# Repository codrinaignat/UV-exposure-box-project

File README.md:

# UV-exposure-box-project

Project structure:
- Proteus folder: contains the Proteus simulation of the schematic for the UV exposure box;
- UV_exposure_box_beta and UV_exposure_box folders contain the PCB and schematic of the project in KiCAD; the beta folder is a more recent version of the project;
- uC program folder contains the MPLABX IDE files for the microcontroller, meaning the C code and additional files;
- Necesare.docx is a list of the necessary components in order to build an UV exposure box from scratch. The list is in Romanian;
- UV_exposure_box.pdf is the schematic of the project, in KiCAD.

The project's purpose is to make the PCB creation process easier. The UV exposure is necessary when you want to create a PCB using a photoresist copper board. 
The box has buttons to set the exposure time, to start and stop the exposure.

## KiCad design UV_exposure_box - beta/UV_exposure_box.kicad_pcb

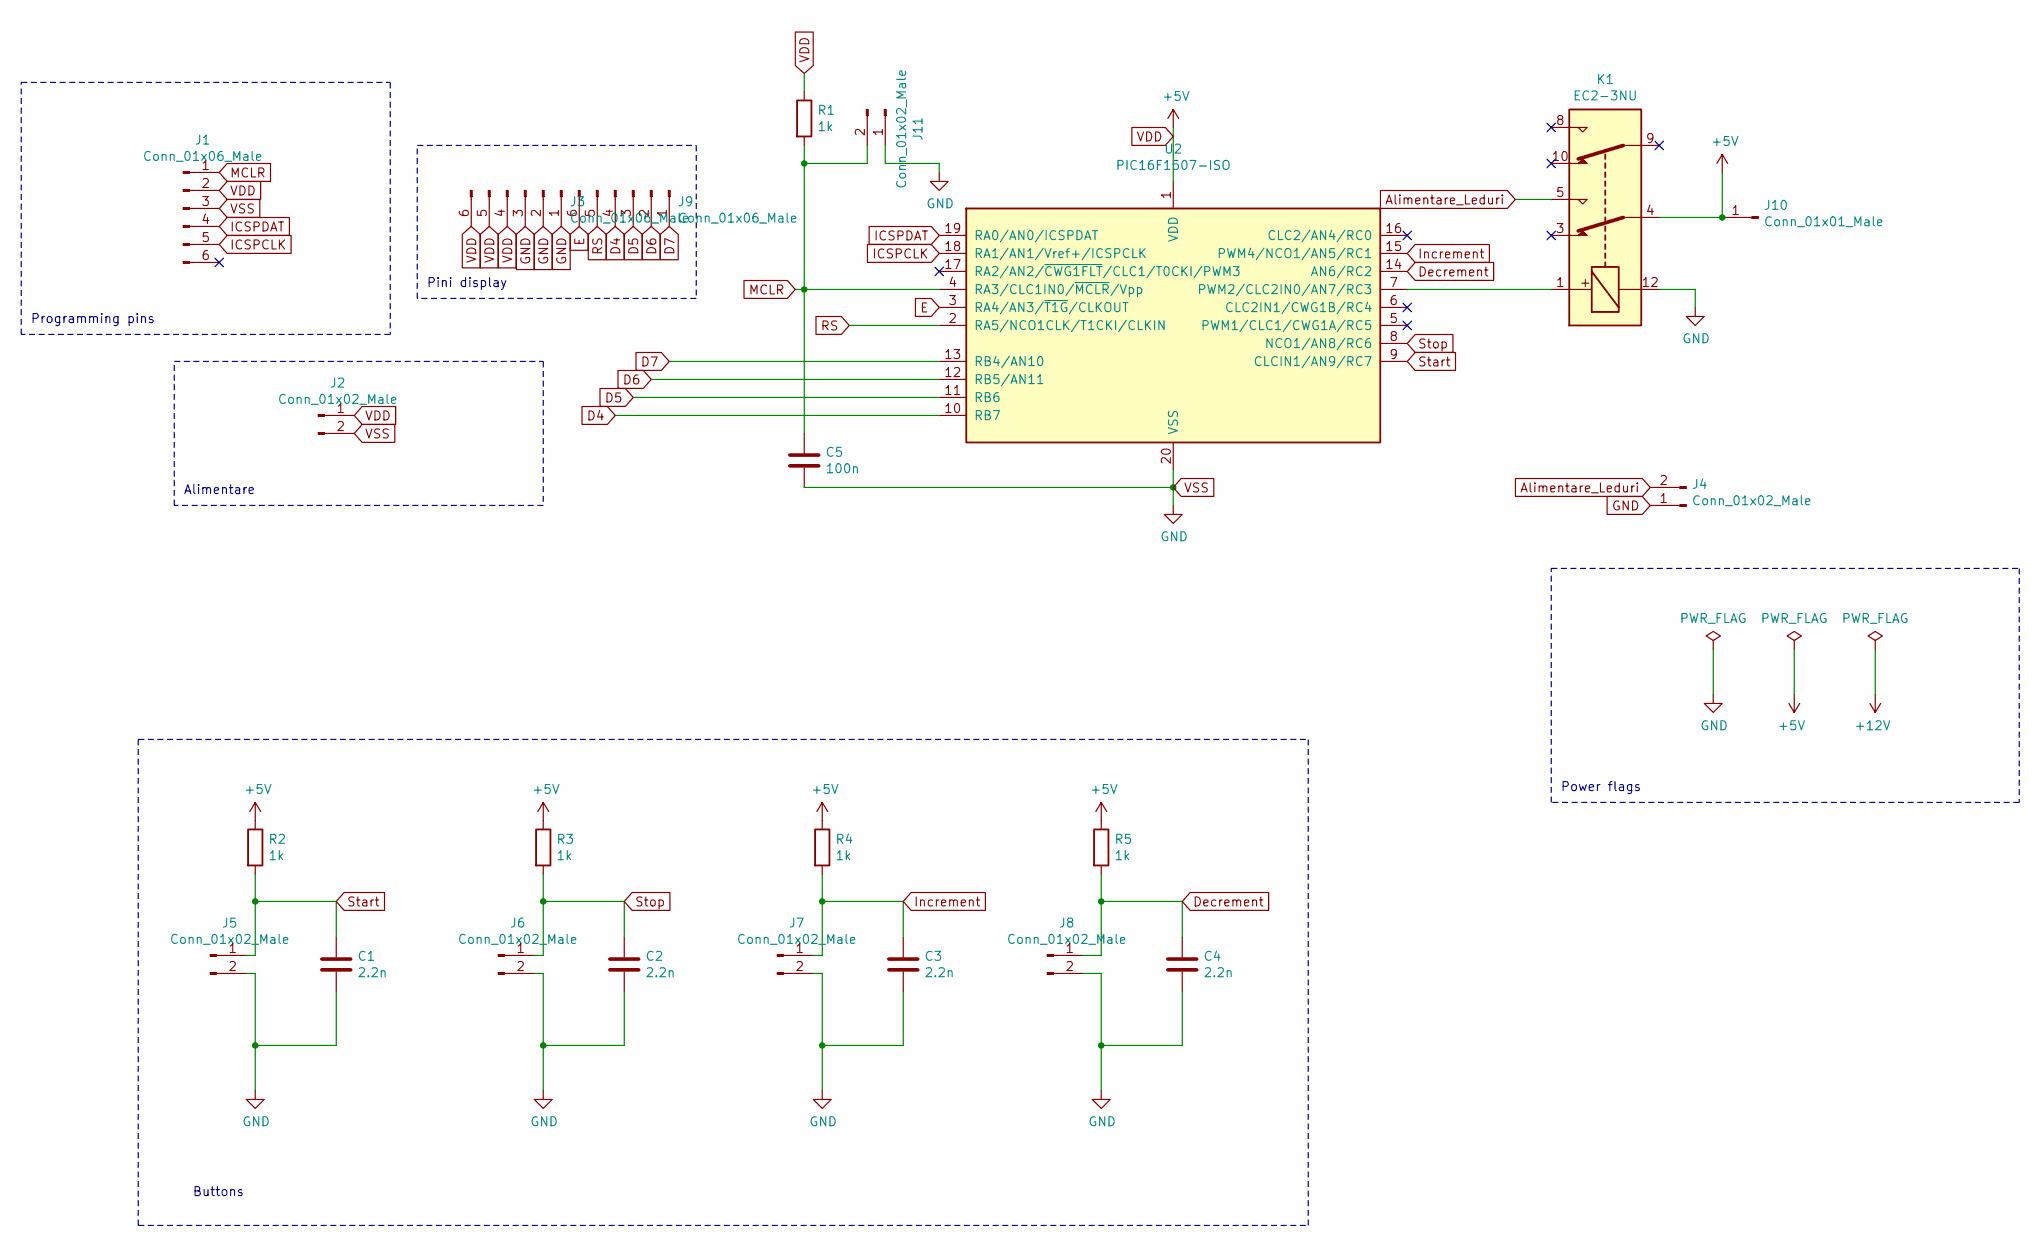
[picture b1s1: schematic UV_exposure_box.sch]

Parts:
C1, C2, C3, C4: 2.2n; C_1206_3216Metric
C5: 100n; C_1206_3216Metric
J1, J3, J9: Conn_01x06_Male; PinHeader_1x06_P2.54mm_Vertical
J2, J4, J5, J6, J7, J8, J11: Conn_01x02_Male; PinHeader_1x02_P2.54mm_Vertical
J10: Conn_01x01_Male; PinHeader_1x01_P2.54mm_Vertical
K1: EC2-3NU; Relay_DPDT_Omron_G6S-2G
R1, R2, R3, R4, R5: 1k; R_1206_3216Metric
U2: PIC16F1507-ISO; SOIC-20W_7.5x12.8mm_P1.27mm

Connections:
Alimentare_Leduri: J4.2, K1.5
D4: J9.4, U2.10 (RB7)
D5: J9.3, U2.11 (RB6)
D6: J9.2, U2.12 (RB5/AN11)
D7: J9.1, U2.13 (RB4/AN10)
Decrement: C4.1, J8.1, R5.2, U2.14 (AN6/RC2)
E: J9.6, U2.3 (RA4/AN3/~T1G~/CLKOUT)
GND: C1.2, C2.2, C3.2, C4.2, C5.2, J1.3, J2.2, J3.1, J3.2, J3.3, J4.1, J5.2, J6.2, J7.2, J8.2, J11.1, K1.12, U2.20 (VSS)
ICSPCLK: J1.5, U2.18 (RA1/AN1/Vref+/ICSPCLK)
ICSPDAT: J1.4, U2.19 (RA0/AN0/ICSPDAT)
Increment: C3.1, J7.1, R4.2, U2.15 (PWM4/NCO1/AN5/RC1)
MCLR: C5.1, J1.1, J11.2, R1.2, U2.4 (RA3/CLC1IN0/~MCLR~/Vpp)
unnamed: K1.1, U2.7 (PWM2/CLC2IN0/AN7/RC3)
RS: J9.5, U2.2 (RA5/NCO1CLK/T1CKI/CLKIN)
Start: C1.1, J5.1, R2.2, U2.9 (CLCIN1/AN9/RC7)
Stop: C2.1, J6.1, R3.2, U2.8 (NCO1/AN8/RC6)
VDD: J1.2, J2.1, J3.4, J3.5, J3.6, J10.1, K1.4, R1.1, R2.1, R3.1, R4.1, R5.1, U2.1 (VDD)

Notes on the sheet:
Programming pins
Alimentare
Power flags
Pini display
Buttons

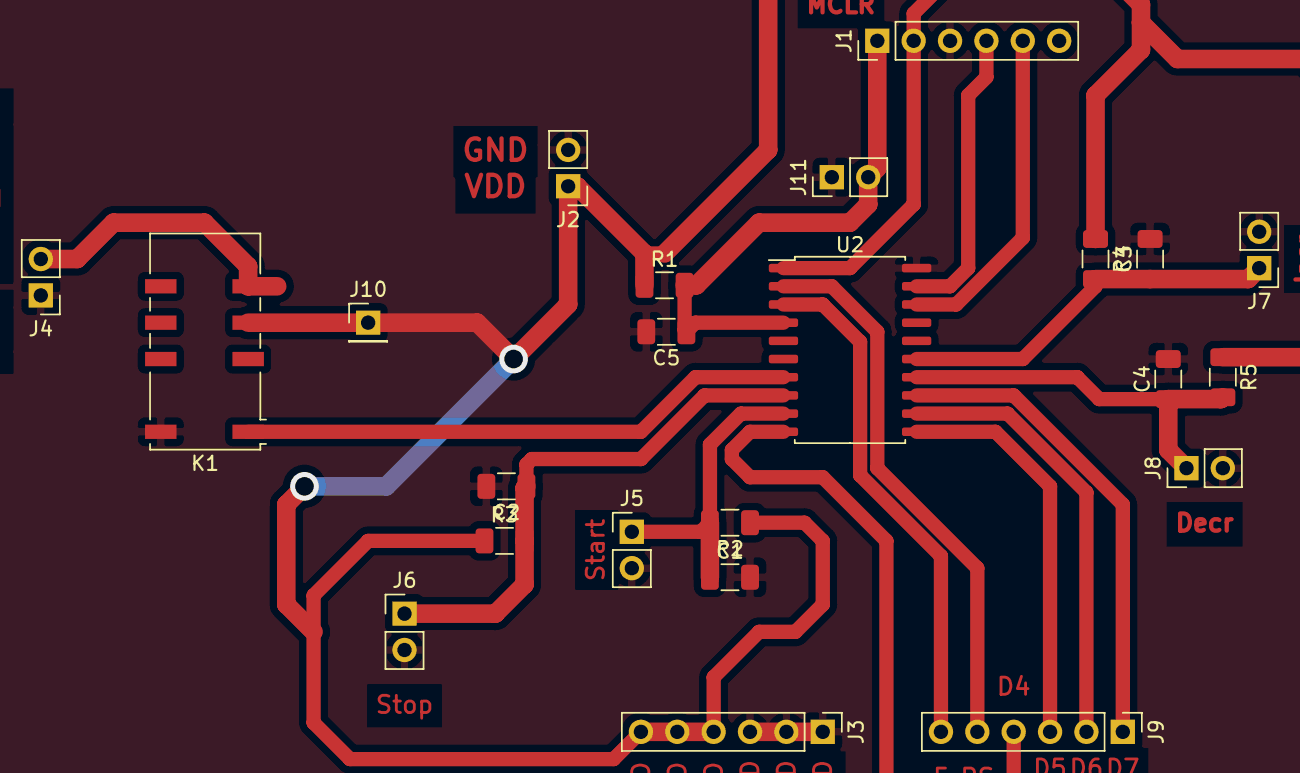
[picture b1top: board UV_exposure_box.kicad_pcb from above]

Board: 2 copper layers, 23 parts (0 on the bottom side), 17 nets.

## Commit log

2023-08-31 no message
